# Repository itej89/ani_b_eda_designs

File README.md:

Hardware designs for Ani-B project
=======================
Welcome to the **A.n.i B** Hardware Design repository. The repository is to maintain designs for boards to meet the control and power management needs of a light weight computer with spacial motion.

This repository contains the design files for two boards: the servo driver board (Ani-B-Servo) and the power management board (Ani-B-Power). The servo driver board can drive a single servo, while the power management board takes data from an SBC (Single-Board Computer) via UART, processes it, and sends relevant information to multiple Ani-B-Servo boards via I2C. Additionally, the power management board manages a 3-cell BMS (Battery Management System), controls charging of the battery, and implements button control for power and attention management.

**Table of Contents**
=======================
1. [Componenets](#componenets)
2. [Hardware Requirements](#hardware-requirements)
3. [Software Requirements](#software-requirements)
4. [Getting Started](#getting-started)
5. [Contributing](#contributing)

**Componenets**
-------------

* Ani-B-Servo control board:
	+ Drives a single servo with PWM output
	+ Accept and perform the servo motion on a requested easing path
	+ Power and signal control of a servo
	+ Compact design for easy installation in small spaces
	+ Uses Atmega328 microcontroller
    + 

* Ani-B-Power control board:
	+ Receives data from SBC via UART 
	+ Parse and filters data as needed
	+ Sends relevant information to multiple Ani-B-Servo boards via I2C 
	+ Manages 3-cell BMS for safe shutdown
	+ Controls charging of the battery
	+ Raises power control and logic control button events
    + 

**Hardware Requirements**
-------------------------

* A PC with KiCad installed
* Atmega328 microcontrollers for Ani-B-Servo boards
* Various electronic components

**Software Requirements**
-------------------------

* KiCad 6.0 or later

**Getting Started**
-------------------

1. Clone this repository to your local machine using `git clone 
https://github.com/your-username/anib-project.git`
2. Open KiCad and create a new project from the cloned repository
3. Start designing the boards by adding components, wires, and other features as needed

**How to Contribute**
--------------------

If you would like to contribute to this repository, please follow these steps:

1. **Fork the repository**: Click the "Fork" button on GitHub to create a copy of this 
repository.
2. **Design and prototype**: Design and prototype your component using CAD software and 
manufacturing techniques.
3. **Submit a pull request**: Submit a pull request with your new design and any modifications 
you made to existing components.

**License**
-----------

This repository is licensed under the [GNU GENERAL PUBLIC LICENSE](https://github.com/itej89/ani_b_mech_designs/blob/main/LICENSE). See 
`LICENSE.md` for details.

**Acknowledgments**
------------------

* This repository is created and maintained by the original designer of A.n.i B

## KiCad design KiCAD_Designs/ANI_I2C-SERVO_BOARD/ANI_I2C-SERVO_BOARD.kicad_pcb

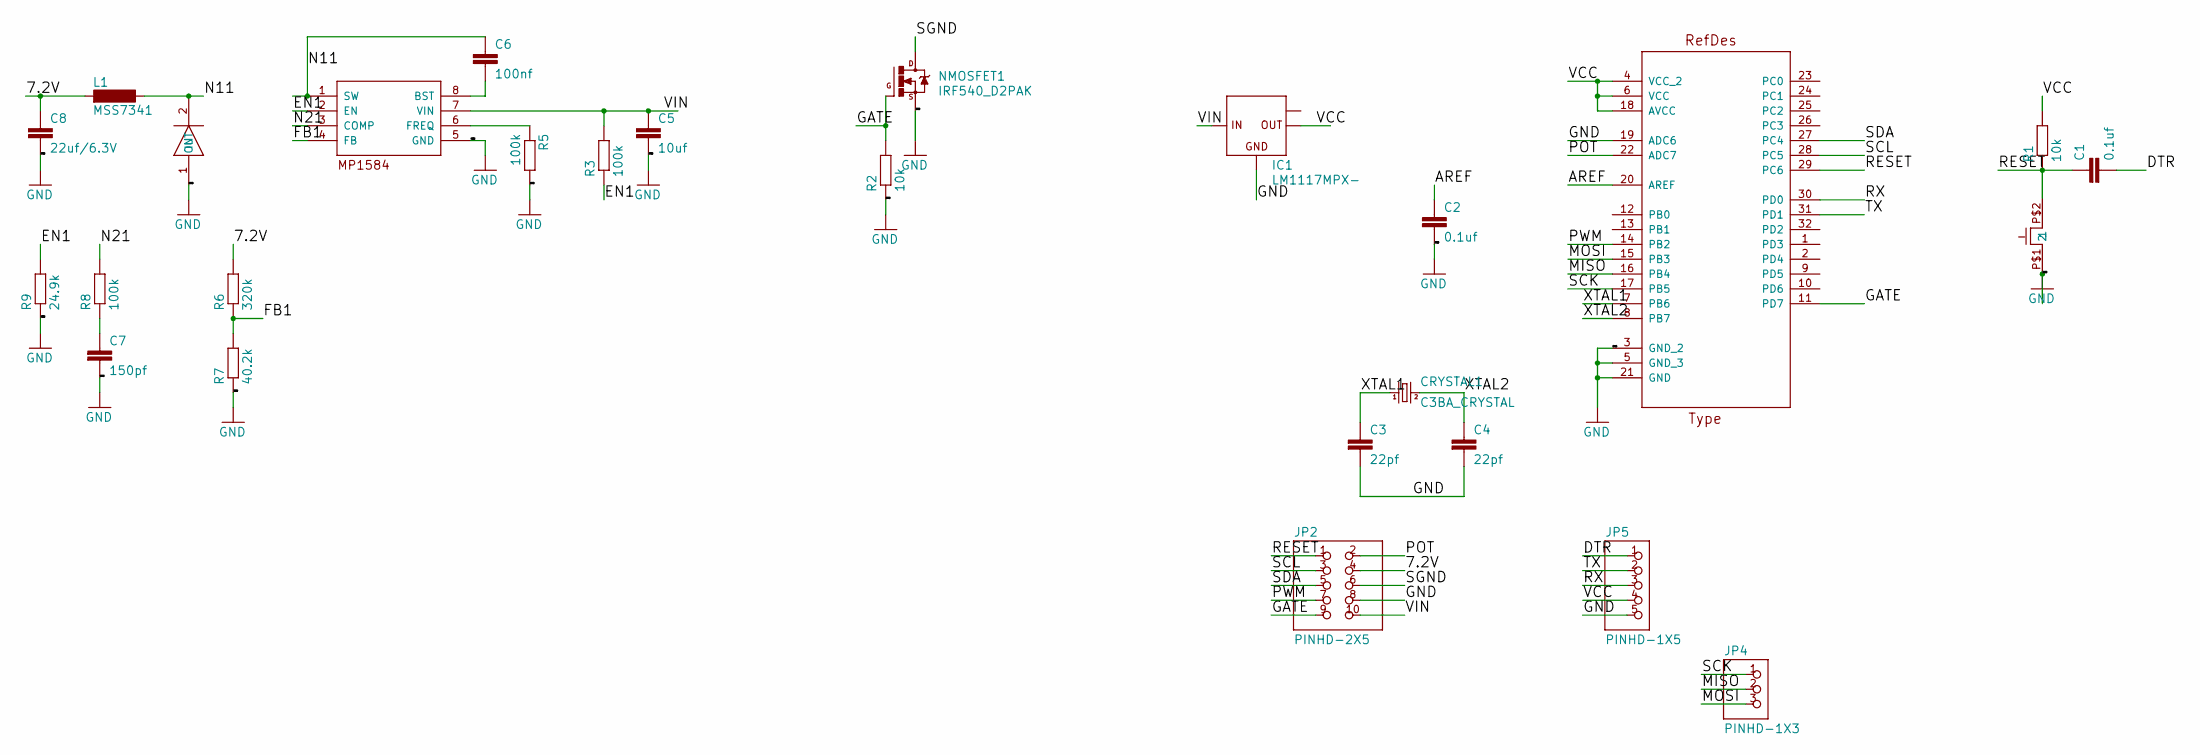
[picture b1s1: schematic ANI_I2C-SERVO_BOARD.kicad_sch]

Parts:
C1, C2: 0.1uf; C0603
C3, C4: 22pf; C0603
C5: 10uf; C0805
C6: 100nf; C0603
C7: 150pf; C0603
C8: 22uf/6.3V; C0805
CONTROLLER1: ATMEGA328P-AU; QFP80P900X900X120-32N
CRYSTAL1: C3BA_CRYSTAL; C3BA
IC1: LM1117MPX-; SOT223
JP2: PINHD-2X5; 2X05
JP4: PINHD-1X3; 1X03
JP5: PINHD-1X5; 1X05
L1: MSS7341
MP1584EN_SERVO1: MP1584EN; SOP-8
NMOSFET1: IRF540_D2PAK; D2PAK
R1, R2: 10k; R0603
R3, R5, R8: 100k; R0603
R6: 320k; R0603
R7: 40.2k; R0603
R9: 24.9k; R0603
SS34_1: SMA-SS34/1N5822; SMA-SS34
TACTILE1: RST_SW_3.6X8_0.6X1MM

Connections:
/7.2V: C8.1, JP2.4, L1.1, R6.2
/AREF: C2.1, CONTROLLER1.20 (AREF)
/DTR: C1.2, JP5.1
/EN1: MP1584EN_SERVO1.2 (EN), R3.1, R9.2
/FB1: MP1584EN_SERVO1.4 (FB), R6.1, R7.2
/GATE: CONTROLLER1.11 (PD7), JP2.9, NMOSFET1.1 (G), R2.2
/MISO: CONTROLLER1.16 (PB4), JP4.2
/MOSI: CONTROLLER1.15 (PB3), JP4.3
/N11: C6.1, L1.2, MP1584EN_SERVO1.1 (SW), SS34_1.2 (OUT)
/N21: MP1584EN_SERVO1.3 (COMP), R8.2
/POT: CONTROLLER1.22 (ADC7), JP2.2
/PWM: CONTROLLER1.14 (PB2), JP2.7
/RESET: C1.1, CONTROLLER1.29 (PC6), JP2.1, R1.1, TACTILE1.P$2 (2)
/RX: CONTROLLER1.30 (PD0), JP5.3
/SCK: CONTROLLER1.17 (PB5), JP4.1
/SCL: CONTROLLER1.28 (PC5), JP2.3
/SDA: CONTROLLER1.27 (PC4), JP2.5
/SGND: JP2.6, NMOSFET1.2 (D)
/TX: CONTROLLER1.31 (PD1), JP5.2
/VCC: CONTROLLER1.4 (VCC_2), CONTROLLER1.6 (VCC), CONTROLLER1.18 (AVCC), IC1.2 (OUT), JP5.4, R1.2
/VIN: C5.1, IC1.3 (IN), JP2.10, MP1584EN_SERVO1.7 (VIN), R3.2
/XTAL1: C3.1, CONTROLLER1.7 (PB6), CRYSTAL1.P$1 (1)
/XTAL2: C4.1, CONTROLLER1.8 (PB7), CRYSTAL1.P$3 (2)
GND: C2.2, C3.2, C4.2, C5.2, C7.2, C8.2, CONTROLLER1.3 (GND_2), CONTROLLER1.5 (GND_3), CONTROLLER1.19 (ADC6), CONTROLLER1.21 (GND), IC1.1 (GND), JP2.8, JP5.5, MP1584EN_SERVO1.5 (GND), NMOSFET1.3 (S), R2.1, R5.2, R7.1, R9.1, SS34_1.1 (IN), TACTILE1.P$1 (1)
unnamed: C6.2, MP1584EN_SERVO1.8 (BST)
unnamed: C7.1, R8.1
unnamed: MP1584EN_SERVO1.6 (FREQ), R5.1

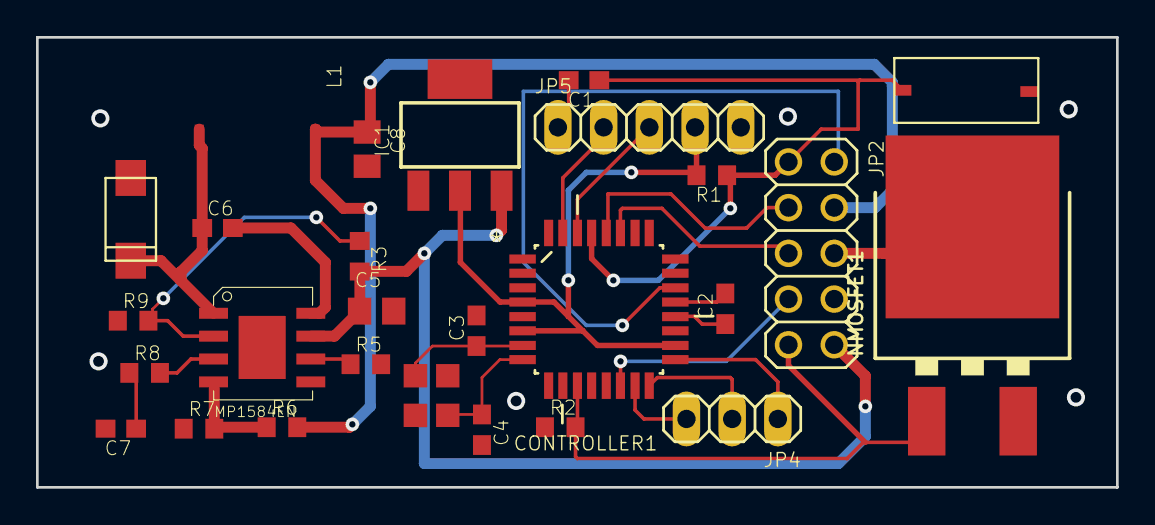
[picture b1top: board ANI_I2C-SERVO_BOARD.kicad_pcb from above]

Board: 2 copper layers, 60.0 x 25.0 mm, 27 parts (0 on the bottom side), 27 nets.

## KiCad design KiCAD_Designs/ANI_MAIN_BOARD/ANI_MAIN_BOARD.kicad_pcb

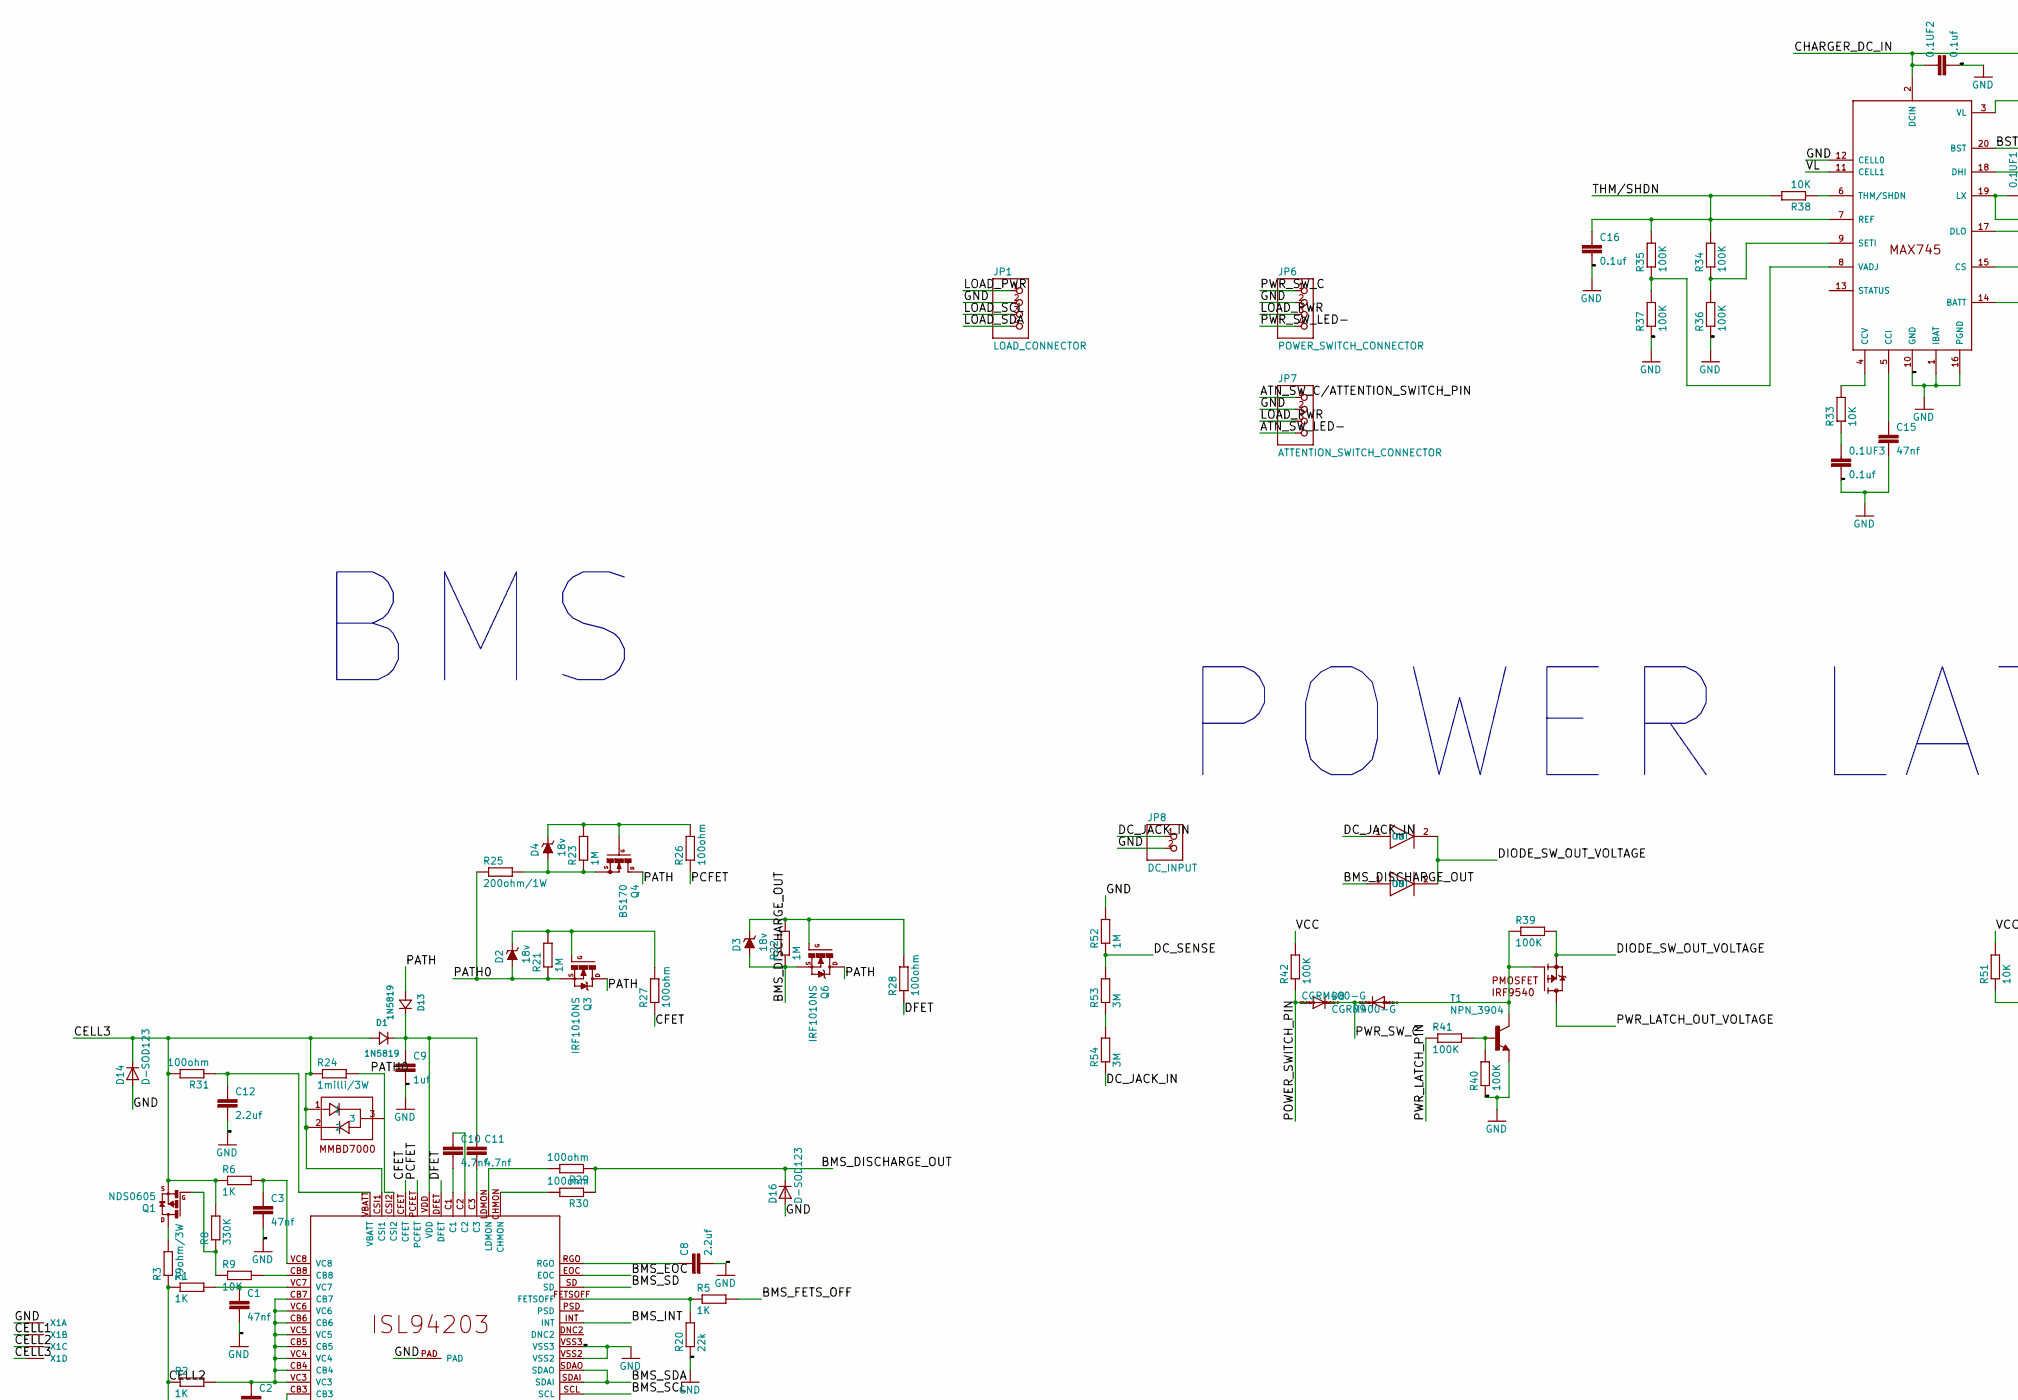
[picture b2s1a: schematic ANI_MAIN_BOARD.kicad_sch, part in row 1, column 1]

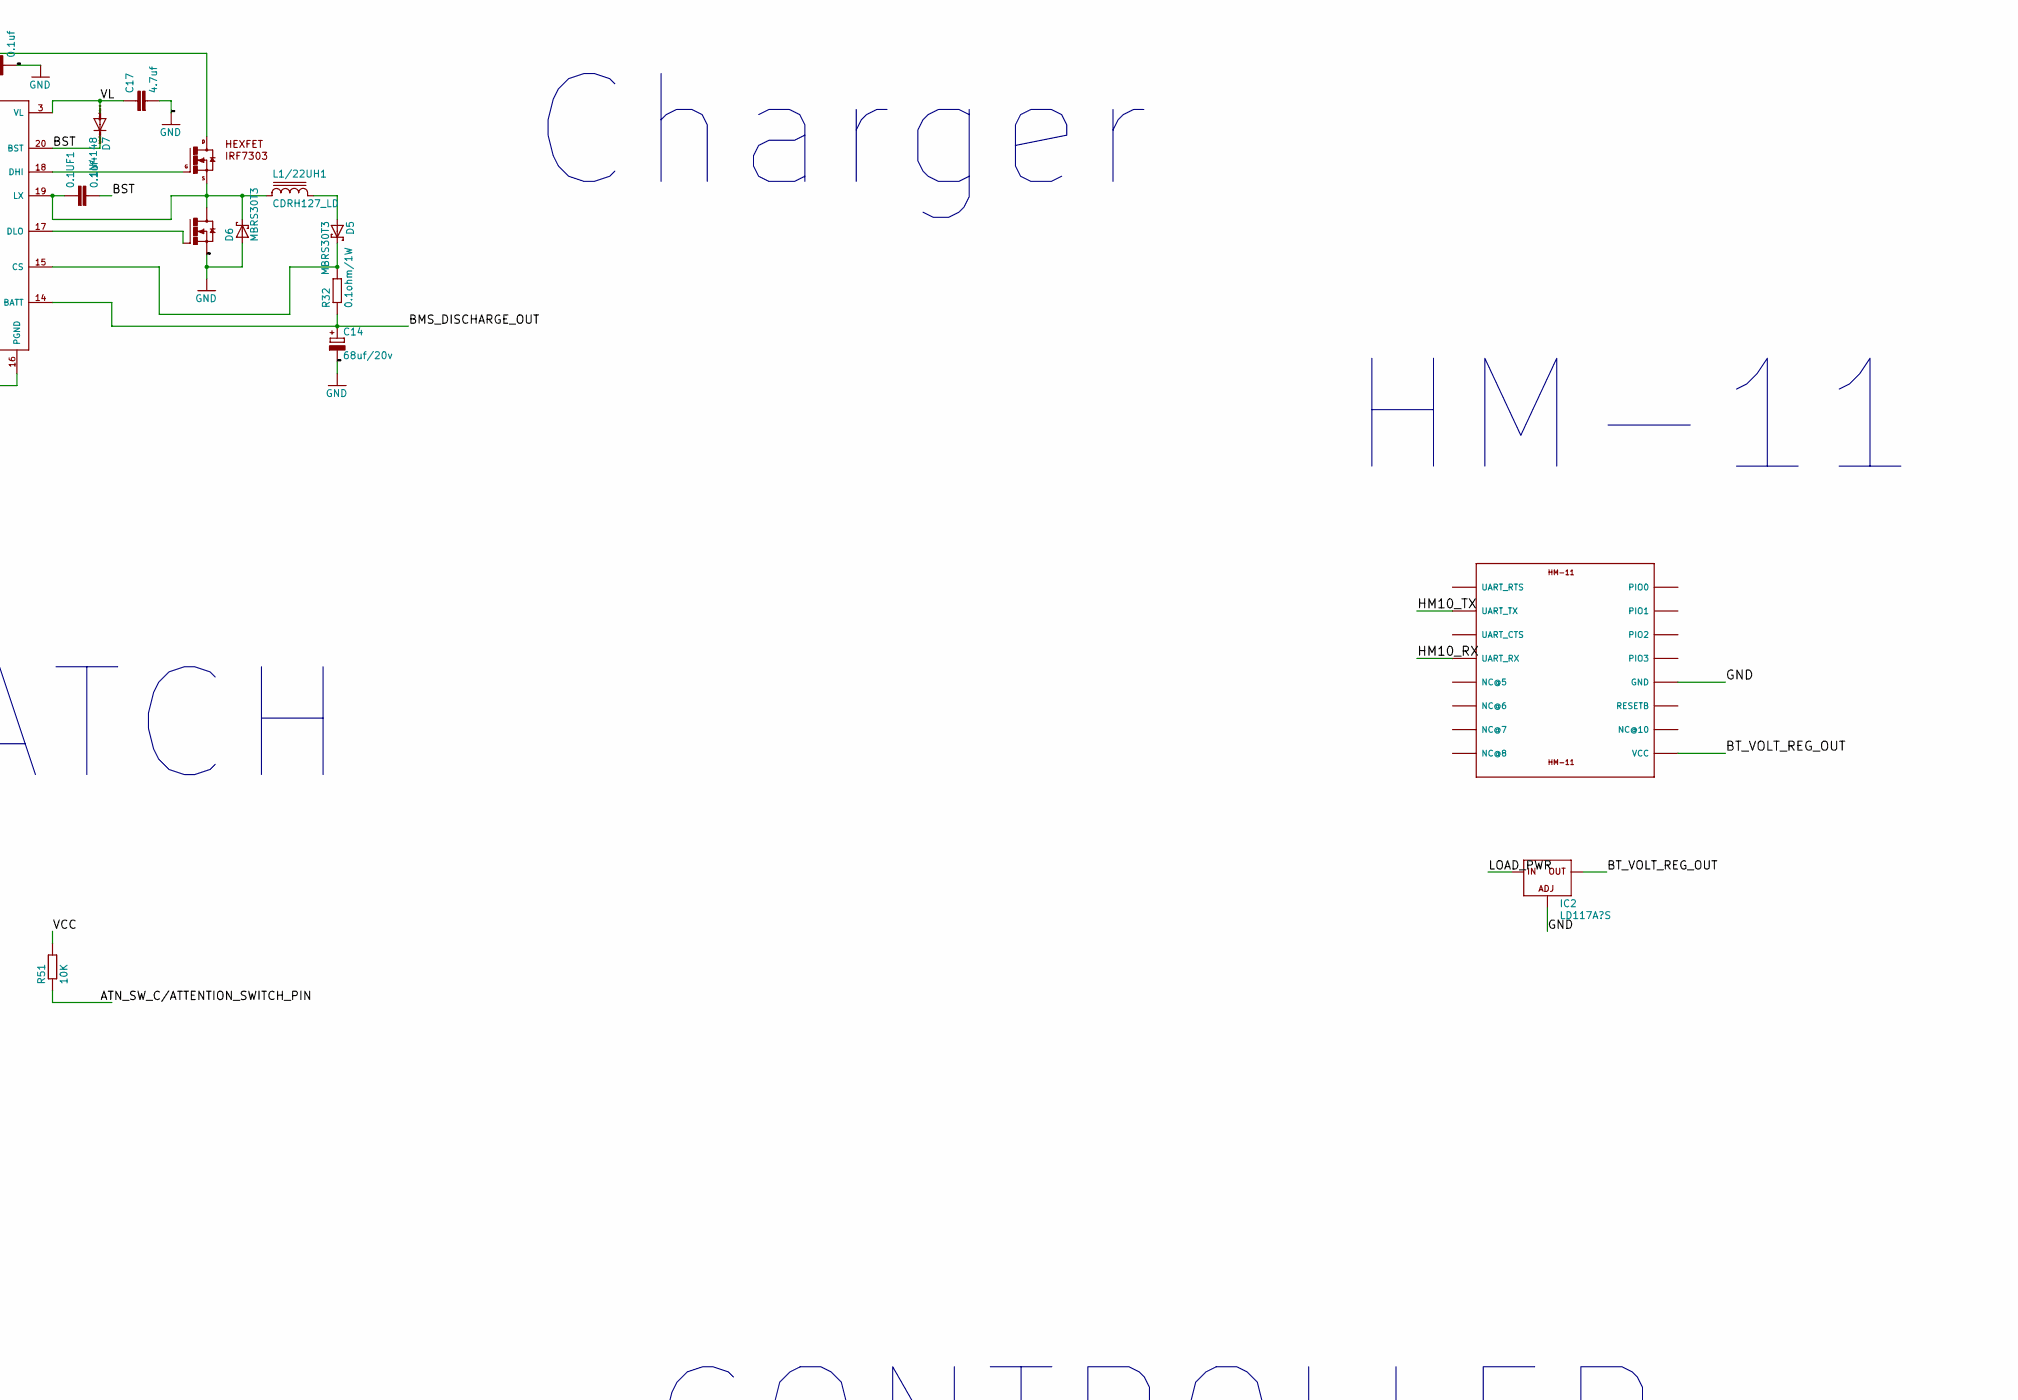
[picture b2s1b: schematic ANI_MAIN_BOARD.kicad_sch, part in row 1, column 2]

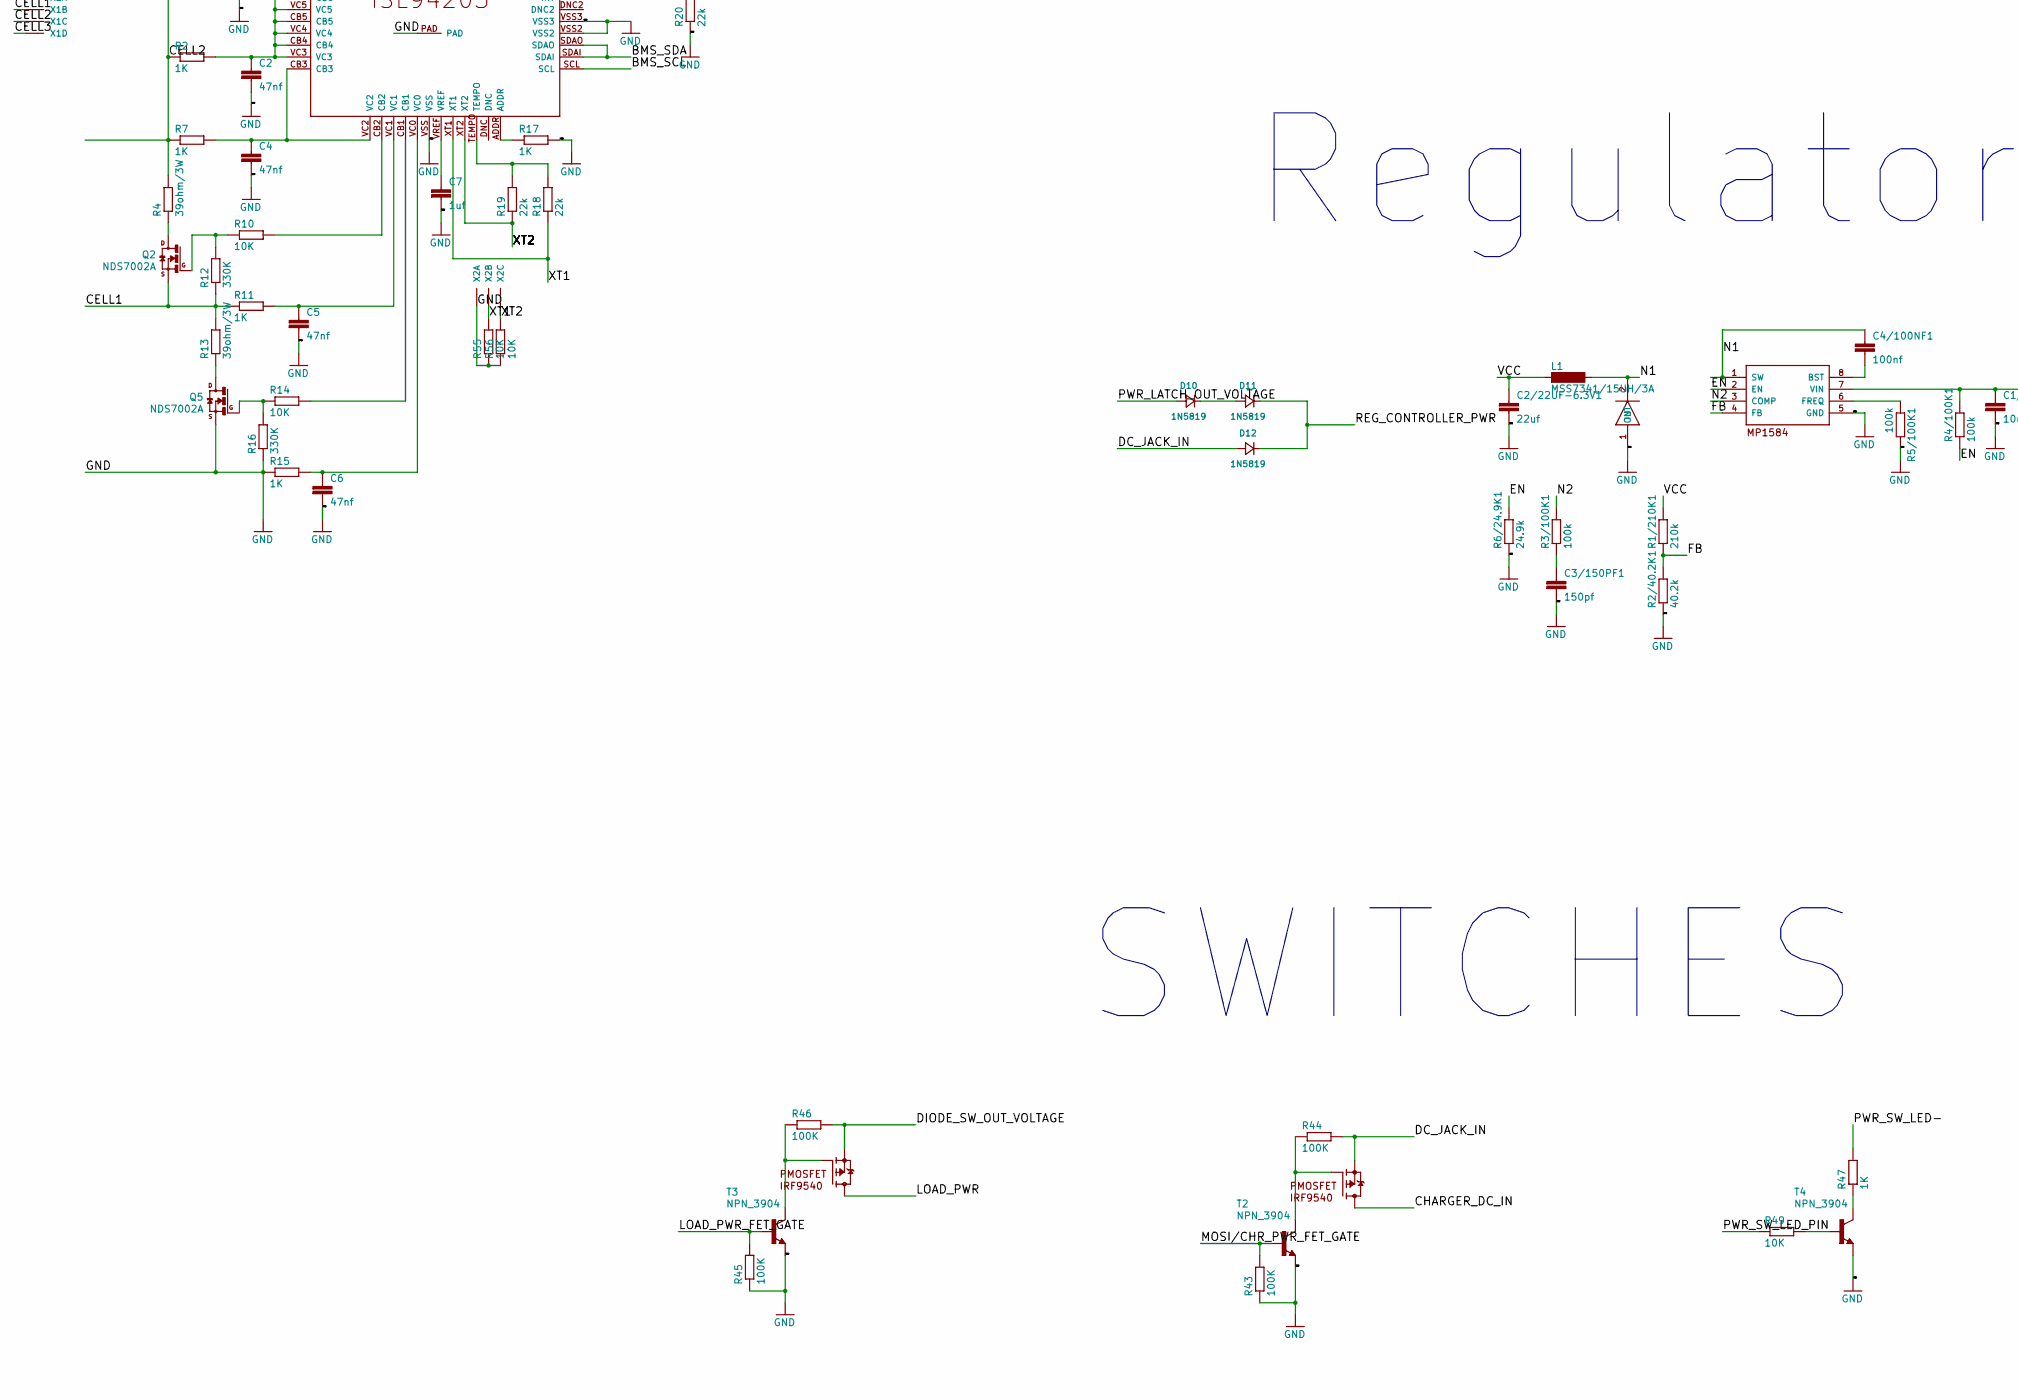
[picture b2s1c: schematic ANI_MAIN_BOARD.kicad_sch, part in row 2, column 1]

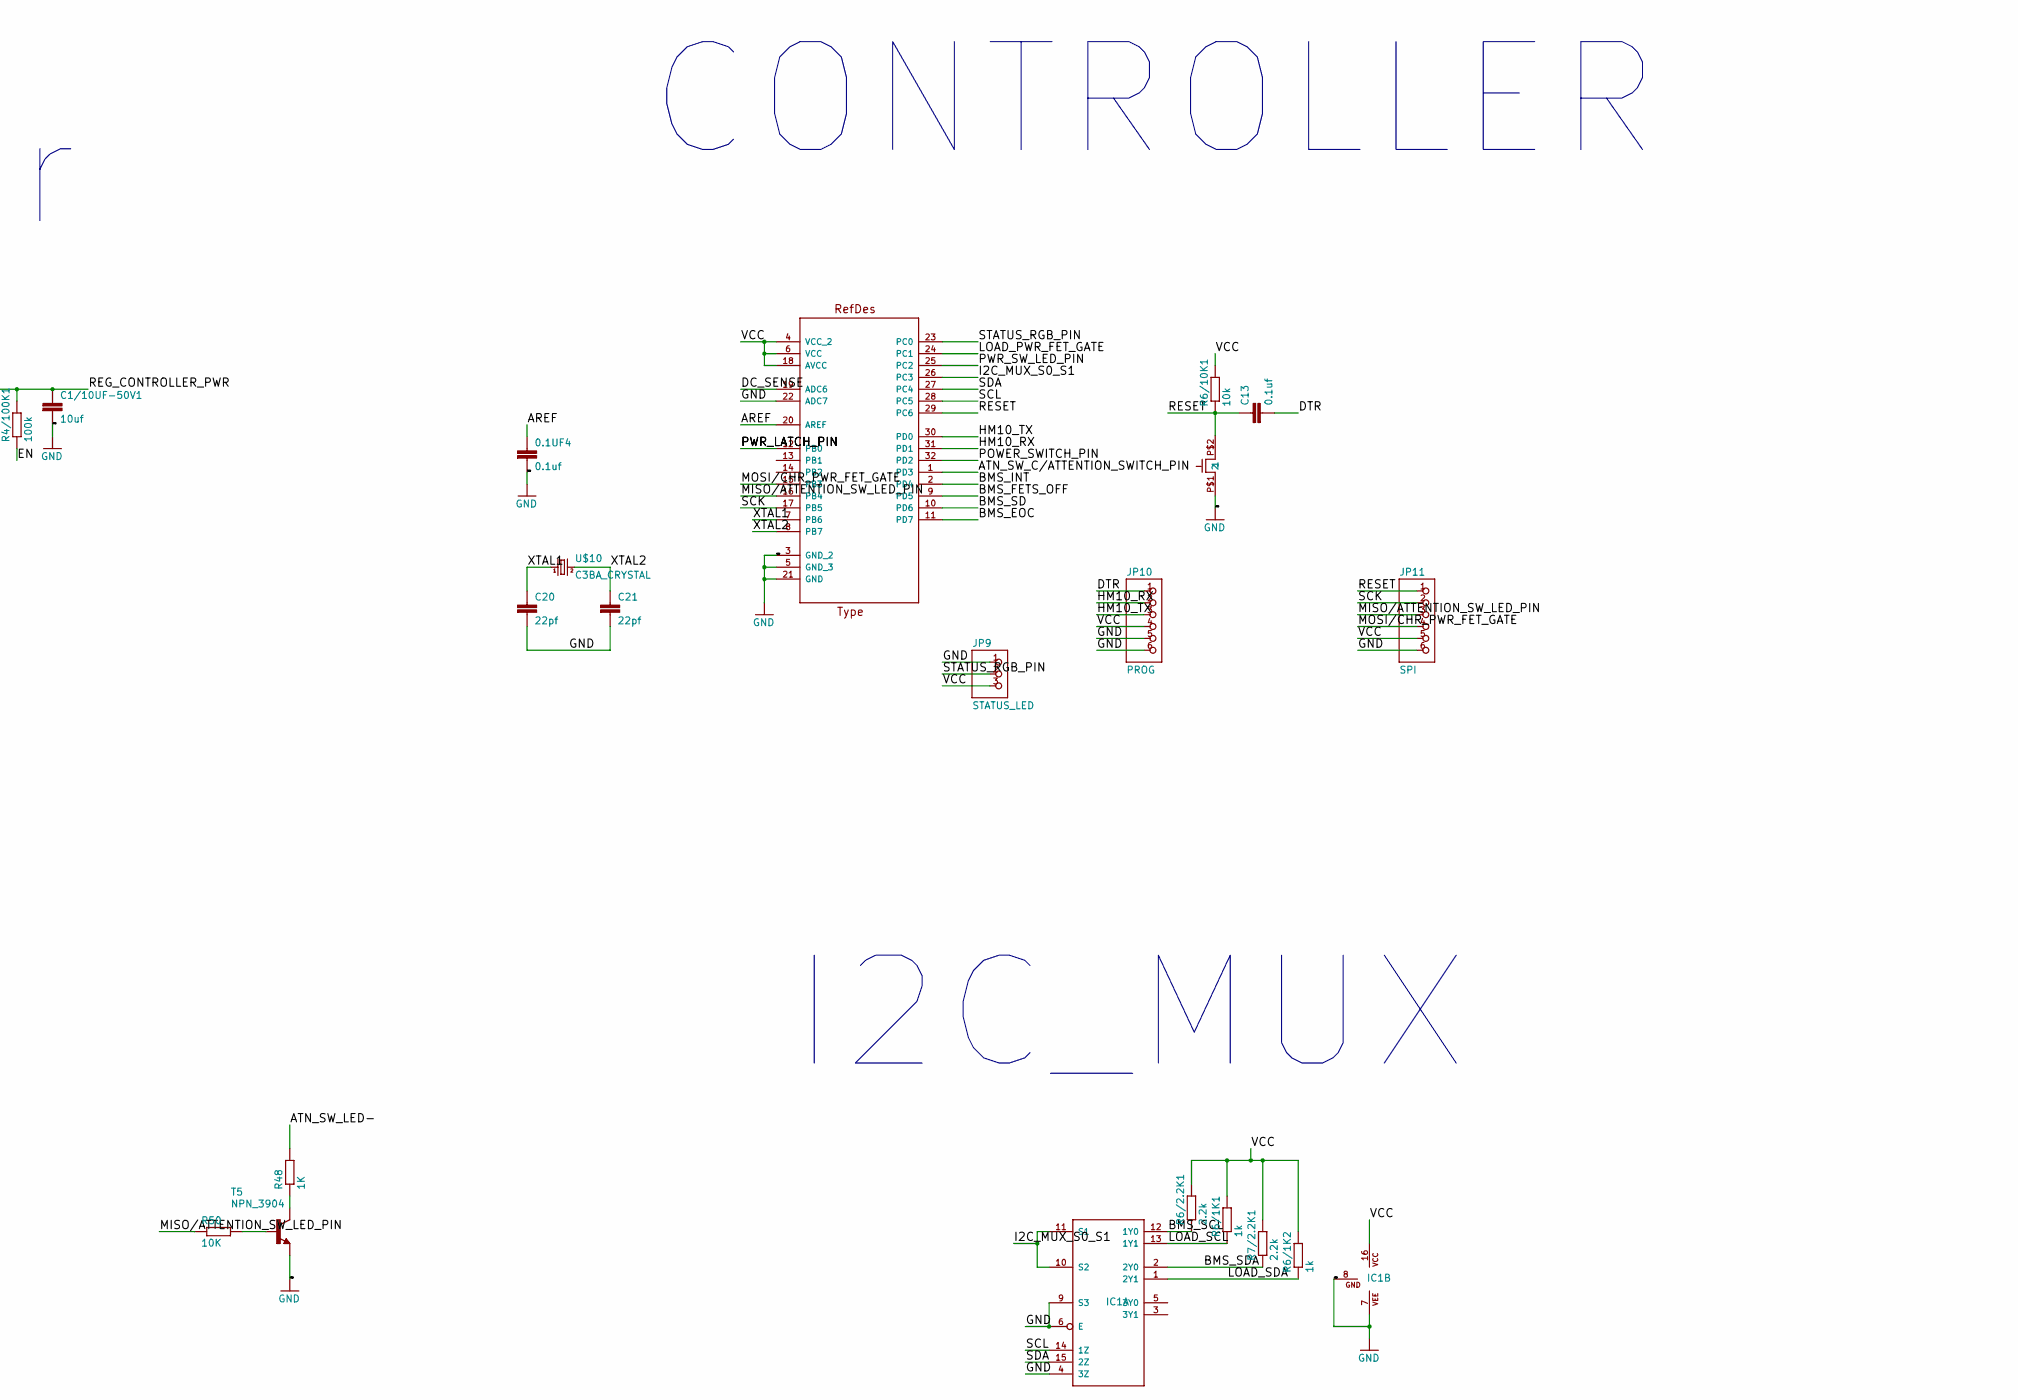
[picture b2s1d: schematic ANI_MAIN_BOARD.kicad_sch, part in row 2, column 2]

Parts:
0.1UF1, 0.1UF2, 0.1UF3, 0.1UF4: 0.1uf; C0603
C1, C2, C3, C4, C5, C6, C15: 47nf; C0603
C1/10UF-50V1: 10uf; C0805
C2/22UF-6.3V1: 22uf; C0805
C3/150PF1: 150pf; C0603
C4/100NF1: 100nf; C0603
C7, C9: 1uf; C0603
C8, C12: 2.2uf; C0603
C10, C11: 4.7nf; C0603
C13, C16: 0.1uf; C0603
C14: 68uf/20v; CT7343
C17: 4.7uf; C0603
C20, C21: 22pf; C0603
D1, D10, D11, D12, D13: 1N5819; DO214
D2, D3, D4: 18v; SOD80C
D5, D6: MBRS30T3; SMC
D7: 1N4148; SOD323-R
D8, D9: CGRM400-G; SOD-123_MINI-SMA
D14, D16: D-SOD123; SOD123
IC1: 744053D; SO16
IC2: LD117A?S; SOT223
JP1: LOAD_CONNECTOR; 1X04_90
JP6: POWER_SWITCH_CONNECTOR; 1X04_90
JP7: ATTENTION_SWITCH_CONNECTOR; 1X04_90
JP8: DC_INPUT; 1X02_90
JP9: STATUS_LED; 1X03_90
JP10: PROG; 1X06_90
JP11: SPI; 1X06_90
L1: MSS7341/15UH/3A; MSS7341
L1/22UH1: CDRH127_LD
Q1: NDS0605; SOT23
Q2, Q5: NDS7002A; SOT23
Q3, Q6: IRF1010NS; D2PAK
Q4: BS170; SOT54E
R1, R2, R5, R6, R7, R11, R15, R17, R47, R48: 1K; R0603
R1/210K1: 210k; R0603
R2/40.2K1: 40.2k; R0603
R3, R4, R13: 39ohm/3W; R6332
R3/100K1, R4/100K1, R5/100K1: 100k; R0603
R6/1K1, R6/1K2: 1k; R0603
R6/2.2K1, R7/2.2K1: 2.2k; R0603
R6/10K1: 10k; R0603
R6/24.9K1: 24.9k; R0603
R8, R12, R16: 330K; R0603
R9, R10, R14, R33, R38, R49, R50, R51, R55, R56: 10K; R0603
R18, R19, R20: 22k; R0603
R21, R22, R23: 1M; R6332
R24: 1milli/3W; R6332
R25: 200ohm/1W; R6332
R26, R27, R28, R29, R30, R31: 100ohm; R0805
R32: 0.1ohm/1W; R2512
R34, R35, R36, R37, R39, R40, R41, R42, R43, R44, R45, R46: 100K; R0603
R52: 1M; R0603
R53, R54: 3M; R0603
SS34: SMA-SS34
T1, T2, T3, T4, T5: NPN_3904; SOT23-BEC
U2: ATMEGA328P-AU; QFP80P900X900X120-32N
U$1: ISL94203
U$2: MAX745; SSOP20
U$3: IRF7303; SO-8
U$4, U$7: SMA-SS34
U$5: RST_SW_3.6X8_0.6X1MM
U$6, U$8, U$11: IRF9540; D2PAK
U$9: MP1584EN; SOP-8
U$10: C3BA_CRYSTAL; C3BA
U$12: HM-11
U$13: MMBD7000; SOT23
X1: JST-XH-04-PIN-LONG-PAD; JST-XH-04-PACKAGE-LONG-PAD
X2: JST-XH-03-PIN-LONG-PAD; JST-XH-03-PACKAGE-LONG-PAD

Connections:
/AREF: 0.1UF4.1, U2.20 (AREF)
/ATN_SW_C/ATTENTION_SWITCH_PIN: JP7.1, R51.1, U2.1 (PD3)
/ATN_SW_LED-: JP7.4, R48.2
/BMS_DISCHARGE_OUT: C14.+, D3.A, D16.1 (C), Q6.3 (S), R22.1, R29.1, R30.1, R32.1, U$2.14 (BATT), U$4.1 (IN)
/BMS_EOC: U2.11 (PD7), U$1.EOC
/BMS_FETS_OFF: R5.2, U2.9 (PD5)
/BMS_INT: U2.2 (PD4), U$1.INT
/BMS_SCL: IC1.12 (1Y0), R6/2.2K1.1, U$1.SCL
/BMS_SD: U2.10 (PD6), U$1.SD
/BMS_SDA: IC1.2 (2Y0), R7/2.2K1.1, U$1.SDAI, U$1.SDAO
/BST: 0.1UF1.2, D7.C, U$2.20 (BST)
/BT_VOLT_REG_OUT: IC2.4 (OUT), U$12.VCC
/CELL1: Q2.2 (S), R11.1, R12.1, R13.2, X1.2
/CELL2: R1.1, R2.1, R3.1, R4.2, R7.1, X1.3
/CELL3: D1.ANODE, D14.1 (C), Q1.2 (S), R6.1, R8.2, R24.1, R31.2, U$1.CSI1, U$13.1, X1.4
/CFET: R27.1, U$1.CFET
/CHARGER_DC_IN: 0.1UF2.1, U$2.2 (DCIN), U$3.7 (D1), U$3.8 (D1), U$8.2 (D)
/DC_JACK_IN: D12.ANODE, JP8.1, R44.2, R54.1, U$7.1 (IN), U$8.3 (S)
/DC_SENSE: R52.1, R53.2, U2.19 (ADC6)
/DFET: R28.1, U$1.DFET
/DIODE_SW_OUT_VOLTAGE: R39.2, R46.2, U$4.2 (OUT), U$6.3 (S), U$7.2 (OUT), U$11.3 (S)
/DTR: C13.2, JP10.1
/EN: R4/100K1.1, R6/24.9K1.2, U$9.2 (EN)
/FB: R1/210K1.1, R2/40.2K1.2, U$9.4 (FB)
/HM10_RX: JP10.2, U2.31 (PD1), U$12.UART_RX
/HM10_TX: JP10.3, U2.30 (PD0), U$12.UART_TX
/I2C_MUX_S0_S1: IC1.10 (S2), IC1.11 (S1), U2.26 (PC3)
/LOAD_PWR: IC2.3 (IN), JP1.1, JP6.3, JP7.3, U$11.2 (D)
/LOAD_PWR_FET_GATE: R45.2, T3.B, U2.24 (PC1)
/LOAD_SCL: IC1.13 (1Y1), JP1.3, R6/1K1.1
/LOAD_SDA: IC1.1 (2Y1), JP1.4, R6/1K2.1
/MISO/ATTENTION_SW_LED_PIN: JP11.3, R50.1, U2.16 (PB4)
/MOSI/CHR_PWR_FET_GATE: JP11.4, R43.2, T2.B, U2.15 (PB3)
/N1: C4/100NF1.1, L1.2, SS34.2 (OUT), U$9.1 (SW)
/N2: R3/100K1.2, U$9.3 (COMP)
/PATH: D13.ANODE, Q3.2 (D), Q4.D, Q6.2 (D)
/PATH0: D2.A, Q3.3 (S), R21.1, R24.2, R25.1, U$1.CSI2
/PCFET: R26.1, U$1.PCFET
/POWER_SWITCH_PIN: D8.A, R42.1, U2.32 (PD2)
/PWR_LATCH_OUT_VOLTAGE: D10.ANODE, U$6.2 (D)
/PWR_LATCH_PIN: R41.1, U2.12 (PB0)
/PWR_SW_C: D8.C, D9.C, JP6.1
/PWR_SW_LED-: JP6.4, R47.2
/PWR_SW_LED_PIN: R49.1, U2.25 (PC2)
/REG_CONTROLLER_PWR: C1/10UF-50V1.1, D11.CATHODE, D12.CATHODE, R4/100K1.2, U$9.7 (VIN)
/RESET: C13.1, JP11.1, R6/10K1.1, U2.29 (PC6), U$5.P$2 (2)
/SCK: JP11.2, U2.17 (PB5)
/SCL: IC1.14 (1Z), U2.28 (PC5)
/SDA: IC1.15 (2Z), U2.27 (PC4)
/STATUS_RGB_PIN: JP9.2, U2.23 (PC0)
/THM/SHDN: C16.1, R34.2, R35.2, R38.2, U$2.7 (REF)
/VCC: C2/22UF-6.3V1.1, IC1.16 (VCC), JP9.3, JP10.4, JP11.5, L1.1, R1/210K1.2, R6/1K1.2, R6/1K2.2, R6/2.2K1.2, R6/10K1.2, R7/2.2K1.2, R42.2, R51.2, U2.4 (VCC_2), U2.6 (VCC), U2.18 (AVCC)
/VL: C17.1, D7.A, U$2.3 (VL), U$2.11 (CELL1)
/XT1: R18.1, R55.2, U$1.XT1, X2.2
/XT2: R19.1, R56.2, U$1.XT2, X2.3
/XTAL1: C20.1, U2.7 (PB6), U$10.P$1 (1)
/XTAL2: C21.1, U2.8 (PB7), U$10.P$3 (2)
GND: 0.1UF2.2, 0.1UF3.2, 0.1UF4.2, C1.2, C1/10UF-50V1.2, C2.2, C2/22UF-6.3V1.2, C3.2, C3/150PF1.2, C4.2, C5.2, C6.2, C7.2, C8.2, C9.2, C12.2, C14.-, C15.2, C16.2, C17.2, C20.2, C21.2, D6.A, D14.2 (A), D16.2 (A), IC1.4 (3Z), IC1.6 (E), IC1.7 (VEE), IC1.8 (GND), IC1.9 (S3), IC2.1 (ADJ), JP1.2, JP6.2, JP7.2, JP8.2, JP9.1, JP10.5, JP10.6, JP11.6, Q5.2 (S), R2/40.2K1.1, R5/100K1.2, R6/24.9K1.1, R15.1, R16.1, R17.2, R20.1, R36.1, R37.1, R40.1, R43.1, R45.1, R52.2, R55.1, R56.1, SS34.1 (IN), T1.E, T2.E, T3.E, T4.E, T5.E, U2.3 (GND_2), U2.5 (GND_3), U2.21 (GND), U2.22 (ADC7), U$1.PAD, U$1.VSS, U$1.VSS2, U$1.VSS3, U$2.1 (IBAT), U$2.10 (GND), U$2.12 (CELL0), U$2.16 (PGND), U$3.3 (S2), U$5.P$1 (1), U$9.5 (GND), U$12.GND, X1.1, X2.1
unnamed: 0.1UF1.1, D6.C, L1/22UH1.1, U$2.19 (LX), U$3.1 (S1), U$3.5 (D2), U$3.6 (D2)
unnamed: 0.1UF3.1, R33.1
unnamed: C1.1, R1.2, U$1.VC7
unnamed: C2.1, R2.2, U$1.CB4, U$1.CB5, U$1.CB6, U$1.CB7, U$1.VC3, U$1.VC4, U$1.VC5, U$1.VC6
unnamed: C3.1, R6.2, U$1.VC8
unnamed: C3/150PF1.1, R3/100K1.1
unnamed: C4.1, R7.2, U$1.CB3, U$1.VC2
unnamed: C4/100NF1.2, U$9.8 (BST)
unnamed: C5.1, R11.2, U$1.VC1
unnamed: C6.1, R15.2, U$1.VC0
unnamed: C7.1, U$1.VREF
unnamed: C8.1, U$1.RGO
unnamed: C10.1, U$1.C2
unnamed: C10.2, U$1.C1
unnamed: C9.1, C11.1, D1.CATHODE, D13.CATHODE, U$1.VDD
unnamed: C11.2, U$1.C3
unnamed: C12.1, R31.1, U$1.VBATT
unnamed: C15.1, U$2.5 (CCI)
unnamed: D2.C, Q3.1 (G), R21.2, R27.2
unnamed: D3.C, Q6.1 (G), R22.2, R28.2
unnamed: D4.A, Q4.S, R23.1, R25.2
unnamed: D4.C, Q4.G, R23.2, R26.2
unnamed: D5.A, L1/22UH1.2
unnamed: D5.C, R32.2, U$2.15 (CS)
unnamed: D9.A, R39.1, T1.C, U$6.1 (G)
unnamed: D10.CATHODE, D11.ANODE
unnamed: Q1.1 (G), R8.1, R9.1
unnamed: Q1.3 (D), R3.2
unnamed: Q2.1 (G), R10.1, R12.2
unnamed: Q2.3 (D), R4.1
unnamed: Q5.1 (G), R14.1, R16.2
unnamed: Q5.3 (D), R13.1
unnamed: R5/100K1.1, U$9.6 (FREQ)
unnamed: R9.2, U$1.CB8
unnamed: R10.2, U$1.CB2
unnamed: R14.2, U$1.CB1
unnamed: R17.1, U$1.ADDR
unnamed: R18.2, R19.2, U$1.TEMPO
unnamed: R5.1, R20.2, U$1.FETSOFF
unnamed: R29.2, U$1.LDMON
unnamed: R30.2, U$1.CHMON
unnamed: R33.2, U$2.4 (CCV)
unnamed: R34.1, R36.2, U$2.9 (SETI)
unnamed: R35.1, R37.2, U$2.8 (VADJ)
unnamed: R38.1, U$2.6 (THM/SHDN)
unnamed: R40.2, R41.2, T1.B
unnamed: R44.1, T2.C, U$8.1 (G)
unnamed: R46.1, T3.C, U$11.1 (G)
unnamed: R47.1, T4.C
unnamed: R48.1, T5.C
unnamed: R49.2, T4.B
unnamed: R50.2, T5.B
unnamed: R53.1, R54.2
unnamed: U$2.17 (DLO), U$3.4 (G2)
unnamed: U$2.18 (DHI), U$3.2 (G1)

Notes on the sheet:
Charger
SWITCHES
POWER LATCH
Regulator
CONTROLLER
I2C_MUX
BMS
HM-11
